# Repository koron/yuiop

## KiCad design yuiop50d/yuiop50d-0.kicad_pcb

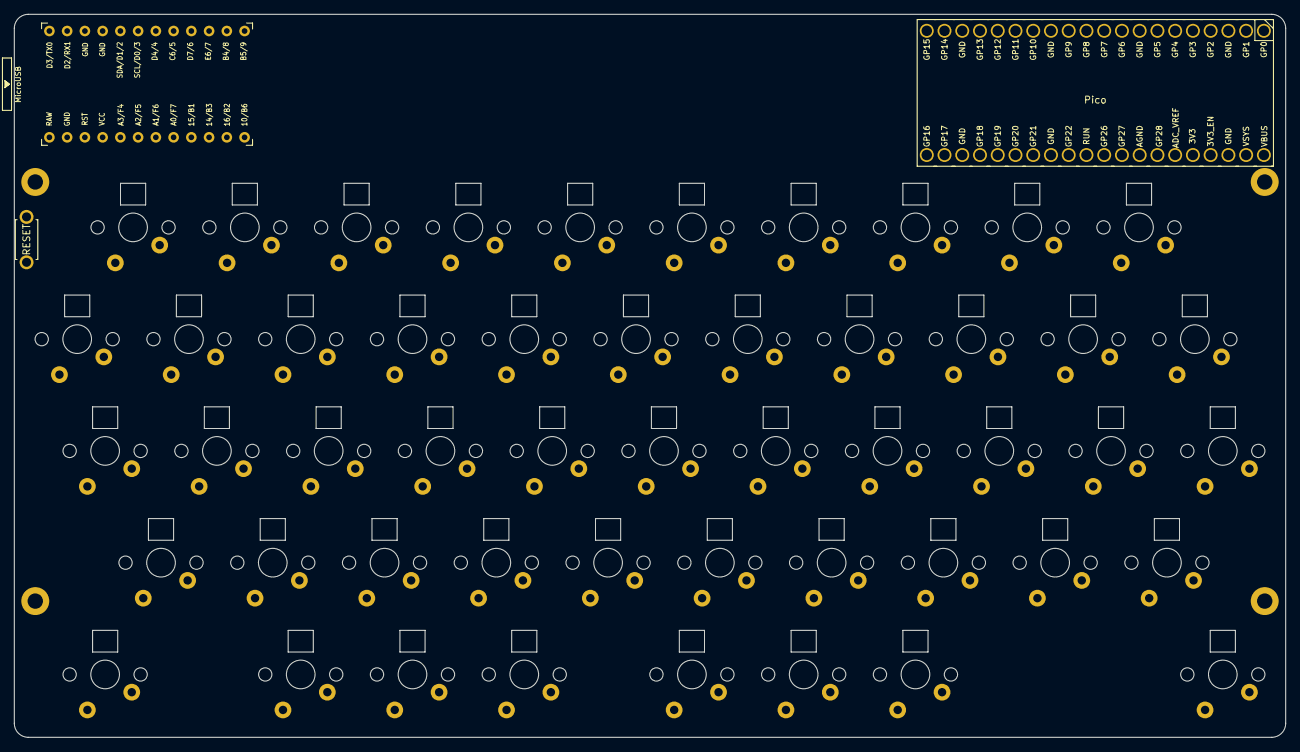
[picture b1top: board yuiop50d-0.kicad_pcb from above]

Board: 2 copper layers, 182.0 x 103.5 mm, 157 parts (0 on the bottom side), 119 nets, no tracks yet.

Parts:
D1, D2, D3, D4, D5, D6, D7, D8, D9, D10, D11, D12, D13, D14, D15, D16, D17, D18, D19, D20, D21, D22, D23, D24, D25, D26, D27, D28, D29, D30, D31, D32, D33, D34, D35, D36, D37, D38, D39, D40, D41, D42, D43, D44, D45, D46, D47, D48, D49, D50: D; D3_SMD_v2_B
HOLE1, HOLE2, HOLE3, HOLE4: Hole_2.2_4
LED1, LED2, LED3, LED4, LED5, LED6, LED7, LED8, LED9, LED10, LED11, LED12, LED13, LED14, LED15, LED16, LED17, LED18, LED19, LED20, LED21, LED22, LED23, LED24, LED25, LED26, LED27, LED28, LED29, LED30, LED31, LED32, LED33, LED34, LED35, LED36, LED37, LED38, LED39, LED40, LED41, LED42, LED43, LED44, LED45, LED46, LED47, LED48, LED49, LED50: YS-SK6812MINI-E; SK6812MINI-E_B
SW1, SW2, SW3, SW4, SW5, SW6, SW7, SW8, SW9, SW10, SW11, SW12, SW13, SW14, SW15, SW16, SW17, SW18, SW19, SW20, SW21, SW22, SW23, SW24, SW25, SW26, SW27, SW28, SW29, SW30, SW31, SW32, SW33, SW34, SW35, SW36, SW37, SW38, SW39, SW40, SW41, SW42, SW43, SW44, SW45, SW46, SW47, SW48, SW49, SW50: SW_PUSH; Switch_CherryMX_Dense_1.00u
SW_RST1: SW_PUSH; ResetSW_2_1side
U1: ProMicro; ProMicro_v3
U2: Pico; RaspberryPi_Pico

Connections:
/COL1: SW1.1, SW11.1, SW22.1, SW33.1, SW43.1, U1.20, U2.7
/COL2: SW2.1, SW12.1, SW23.1, SW34.1, SW44.1, U1.5, U2.9
/COL3: SW3.1, SW13.1, SW24.1, SW35.1, SW45.1, U1.19, U2.10
/COL4: SW4.1, SW14.1, SW25.1, SW36.1, SW46.1, U1.6, U2.11
/COL5: SW5.1, SW15.1, SW26.1, SW37.1, SW47.1, U1.18, U2.12
/COL6: SW6.1, SW16.1, SW27.1, SW38.1, SW48.1, U1.7, U2.14
/COL7: SW7.1, SW17.1, SW28.1, SW39.1, SW49.1, U1.8, U2.15
/COL8: SW8.1, SW18.1, SW29.1, SW40.1, SW50.1, U1.9, U2.16
/COL9: SW9.1, SW19.1, SW30.1, SW41.1, U1.10, U2.17
/COL10: SW10.1, SW20.1, SW31.1, SW42.1, U1.11, U2.19
/COL11: SW21.1, SW32.1, U1.12, U2.20
/LED: LED1.4, U1.1, U2.6
/ROW1: D1.1, D2.1, D3.1, D4.1, D5.1, D6.1, D7.1, D8.1, D9.1, D10.1, U1.17, U2.26
/ROW2: D11.1, D12.1, D13.1, D14.1, D15.1, D16.1, D17.1, D18.1, D19.1, D20.1, D21.1, U1.16, U2.25
/ROW3: D22.1, D23.1, D24.1, D25.1, D26.1, D27.1, D28.1, D29.1, D30.1, D31.1, D32.1, U1.15, U2.24
/ROW4: D33.1, D34.1, D35.1, D36.1, D37.1, D38.1, D39.1, D40.1, D41.1, D42.1, U1.14, U2.22
/ROW5: D43.1, D44.1, D45.1, D46.1, D47.1, D48.1, D49.1, D50.1, U1.13, U2.21
/RST: SW_RST1.1, U1.22
GND: LED1.3, LED2.3, LED3.3, LED4.3, LED5.3, LED6.3, LED7.3, LED8.3, LED9.3, LED10.3, LED11.3, LED12.3, LED13.3, LED14.3, LED15.3, LED16.3, LED17.3, LED18.3, LED19.3, LED20.3, LED21.3, LED22.3, LED23.3, LED24.3, LED25.3, LED26.3, LED27.3, LED28.3, LED29.3, LED30.3, LED31.3, LED32.3, LED33.3, LED34.3, LED35.3, LED36.3, LED37.3, LED38.3, LED39.3, LED40.3, LED41.3, LED42.3, LED43.3, LED44.3, LED45.3, LED46.3, LED47.3, LED48.3, LED49.3, LED50.3, SW_RST1.2, U1.3, U1.4, U1.23, U2.3, U2.8, U2.13, U2.18, U2.23, U2.28, U2.33, U2.38
unnamed: D1.2, SW1.2
unnamed: D2.2, SW2.2
unnamed: D3.2, SW3.2
unnamed: D4.2, SW4.2
unnamed: D5.2, SW5.2
unnamed: D6.2, SW6.2
unnamed: D7.2, SW7.2
unnamed: D8.2, SW8.2
unnamed: D9.2, SW9.2
unnamed: D10.2, SW10.2
unnamed: D11.2, SW11.2
unnamed: D12.2, SW12.2
unnamed: D13.2, SW13.2
unnamed: D14.2, SW14.2
unnamed: D15.2, SW15.2
unnamed: D16.2, SW16.2
unnamed: D17.2, SW17.2
unnamed: D18.2, SW18.2
unnamed: D19.2, SW19.2
unnamed: D20.2, SW20.2
unnamed: D21.2, SW21.2
unnamed: D22.2, SW22.2
unnamed: D23.2, SW23.2
unnamed: D24.2, SW24.2
unnamed: D25.2, SW25.2
unnamed: D26.2, SW26.2
unnamed: D27.2, SW27.2
unnamed: D28.2, SW28.2
unnamed: D29.2, SW29.2
unnamed: D30.2, SW30.2
unnamed: D31.2, SW31.2
unnamed: D32.2, SW32.2
unnamed: D33.2, SW33.2
unnamed: D34.2, SW34.2
unnamed: D35.2, SW35.2
unnamed: D36.2, SW36.2
unnamed: D37.2, SW37.2
unnamed: D38.2, SW38.2
unnamed: D39.2, SW39.2
unnamed: D40.2, SW40.2
unnamed: D41.2, SW41.2
unnamed: D42.2, SW42.2
unnamed: D43.2, SW43.2
unnamed: D44.2, SW44.2
unnamed: D45.2, SW45.2
unnamed: D46.2, SW46.2
unnamed: D47.2, SW47.2
unnamed: D48.2, SW48.2
unnamed: D49.2, SW49.2
unnamed: D50.2, SW50.2
unnamed: LED1.2, LED2.4
unnamed: LED2.2, LED3.4
unnamed: LED3.2, LED4.4
unnamed: LED4.2, LED5.4
unnamed: LED5.2, LED6.4
unnamed: LED6.2, LED7.4
unnamed: LED7.2, LED8.4
unnamed: LED8.2, LED9.4
unnamed: LED10.2, LED11.4
unnamed: LED9.2, LED10.4
unnamed: LED11.2, LED12.4
unnamed: LED12.2, LED13.4
unnamed: LED13.2, LED14.4
unnamed: LED14.2, LED15.4
unnamed: LED15.2, LED16.4
unnamed: LED16.2, LED17.4
unnamed: LED17.2, LED18.4
unnamed: LED18.2, LED19.4
unnamed: LED19.2, LED20.4
unnamed: LED20.2, LED21.4
unnamed: LED21.2, LED22.4
unnamed: LED22.2, LED23.4
unnamed: LED23.2, LED24.4
unnamed: LED24.2, LED25.4
unnamed: LED25.2, LED26.4
unnamed: LED26.2, LED27.4
unnamed: LED27.2, LED28.4
unnamed: LED28.2, LED29.4
unnamed: LED29.2, LED30.4
unnamed: LED30.2, LED31.4
unnamed: LED31.2, LED32.4
unnamed: LED32.2, LED33.4
unnamed: LED33.2, LED34.4
unnamed: LED34.2, LED35.4
unnamed: LED35.2, LED36.4
unnamed: LED36.2, LED37.4
unnamed: LED37.2, LED38.4
unnamed: LED38.2, LED39.4
unnamed: LED39.2, LED40.4
unnamed: LED40.2, LED41.4
unnamed: LED41.2, LED42.4
unnamed: LED42.2, LED43.4
unnamed: LED43.2, LED44.4
unnamed: LED44.2, LED45.4
unnamed: LED45.2, LED46.4
unnamed: LED46.2, LED47.4
unnamed: LED47.2, LED48.4
unnamed: LED48.2, LED49.4
unnamed: LED49.2, LED50.4
VCC: LED1.1, LED2.1, LED3.1, LED4.1, LED5.1, LED6.1, LED7.1, LED8.1, LED9.1, LED10.1, LED11.1, LED12.1, LED13.1, LED14.1, LED15.1, LED16.1, LED17.1, LED18.1, LED19.1, LED20.1, LED21.1, LED22.1, LED23.1, LED24.1, LED25.1, LED26.1, LED27.1, LED28.1, LED29.1, LED30.1, LED31.1, LED32.1, LED33.1, LED34.1, LED35.1, LED36.1, LED37.1, LED38.1, LED39.1, LED40.1, LED41.1, LED42.1, LED43.1, LED44.1, LED45.1, LED46.1, LED47.1, LED48.1, LED49.1, LED50.1, U1.21, U2.36

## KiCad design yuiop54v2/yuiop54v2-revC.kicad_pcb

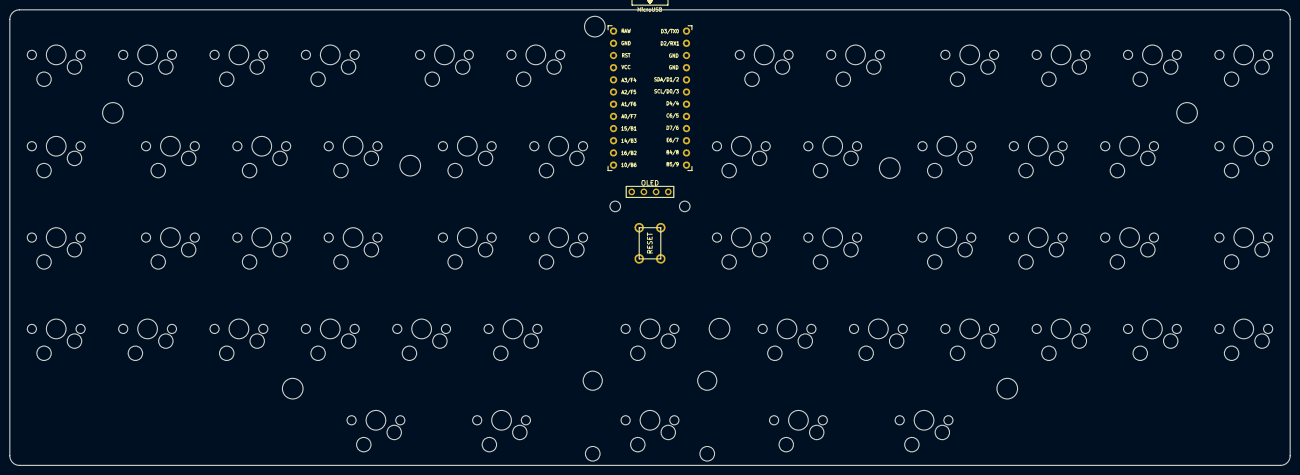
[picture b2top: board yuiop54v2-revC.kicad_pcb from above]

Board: 2 copper layers, 267.0 x 95.0 mm, 57 parts (0 on the bottom side), 11 nets, no tracks yet.

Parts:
OL1: OLED; OLED_128x32
SW1, SW2, SW3, SW4, SW5, SW6, SW7, SW8, SW9, SW10, SW11, SW12, SW14, SW15, SW16, SW17, SW18, SW19, SW20, SW21, SW22, SW23, SW26, SW27, SW28, SW29, SW30, SW31, SW32, SW33, SW34, SW35, SW38, SW39, SW40, SW41, SW42, SW43, SW44, SW45, SW46, SW47: SW_PUSH; Cherry_MX_Hotswap_1u
SW13, SW24, SW25, SW36, SW37, SW48, SW49: SW_PUSH; Cherry_MX_Hotswap_1.0u
SW50, SW54: SW_PUSH; Cherry_MX_Hotswap_1.5u
SW51, SW53: SW_PUSH; Cherry_MX_Hotswap_1.25u
SW52: SW_PUSH; Cherry_MX_Hotswap_2.0u
SW_RST1: SW_PUSH; ResetSW_4_1side
U1: ProMicro; ProMicro_v3

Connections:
/COL1: SW1.1, SW7.1, SW13.1, SW19.1, SW25.1, SW31.1, SW37.1, SW43.1, SW49.1, U1.2
/COL2: SW2.1, SW8.1, SW14.1, SW20.1, SW26.1, SW32.1, SW38.1, SW44.1, SW53.1, U1.7
/COL3: SW3.1, SW9.1, SW15.1, SW21.1, SW27.1, SW33.1, SW39.1, SW45.1, SW54.1, U1.20
/COL4: SW4.1, SW10.1, SW16.1, SW22.1, SW28.1, SW34.1, SW40.1, SW46.1, SW50.1, U1.19
/COL5: SW5.1, SW11.1, SW17.1, SW23.1, SW29.1, SW35.1, SW41.1, SW47.1, SW51.1, U1.18
/COL6: SW6.1, SW12.1, SW18.1, SW24.1, SW30.1, SW36.1, SW42.1, SW48.1, SW52.1, U1.17
/RST: SW_RST1.1, U1.22
/SDA: OL1.1, U1.5
/SDL: OL1.2, U1.6
GND: OL1.4, SW_RST1.2, U1.3, U1.4, U1.23
VCC: OL1.3, U1.21
